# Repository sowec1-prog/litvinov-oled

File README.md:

# Litvínov OLED scoreboard

Autonomní hokejový panel pro **ESP32-C3 SuperMini** a OLED SSD1306 128×64. Firmware čte kompaktní stav z `https://litvinov-server.onrender.com/api/live`; PC ani LVGL nejsou potřeba.

## Funkce

- živé skóre, týmové kódy a poslední střelec bez diakritiky;
- `TRES-LIT`, `TRES-PCE` nebo `TRES-LIT/PCE` podle strukturované události píšťalky;
- přestávka s lokálním odpočtem bez cloudových dotazů;
- lokální odpočet příštího zápasu;
- gól Litvínova: znělka a 30sekundová blikající animace `GOOL` zprava doleva;
- první přijatý gól po restartu animaci ani zvuk nespustí;
- konečný výsledek se na cloudovém API drží pět minut jako `ZAPAS SKONCIL`.

## Použitý hardware

- **ESP32-C3 SuperMini** — ESP32-C3, 4 MB flash, Wi-Fi 2,4 GHz; projekt používá PlatformIO profil `esp32-c3-devkitm-1`.
- **OLED SSD1306 128 × 64 px**, I²C, adresa `0x3C`.
- **Pasivní piezo bzučák** ověřený pro PWM tóny.
- USB datový kabel pro napájení a nahrání firmwaru.
- Propojovací vodiče: 4× pro OLED, 2× pro bzučák.

## Zapojení

Všechny moduly musí mít společnou zem (**GND**). OLED i GPIO ESP32-C3 jsou 3,3 V logika; OLED proto napájejte z pinu **3V3**, ne z 5 V.

| ESP32-C3 SuperMini | Připojit na | Poznámka |
|---|---|---|
| GPIO8 | OLED SDA | I²C data |
| GPIO9 | OLED SCL | I²C hodiny |
| 3V3 | OLED VCC | napájení OLED |
| GND | OLED GND | společná zem |
| GPIO3 | piezo `+` / signál | PWM znělka — opravené zapojení PCB rev. A |
| GND | piezo `-` | společná zem |
| GPIO2 | ADC_BAT z děliče 100 kΩ / 100 kΩ | pouze připravený vstup měření baterie; firmware jej zatím nečte |

OLED používá I²C adresu `0x3C`.

### Oprava osazené PCB rev. A

Deska byla vyrobena s posunem dvou signálů proti původnímu návrhu: PWM bzučáku je na **GPIO3** (ne GPIO4) a uzel `ADC_BAT` děliče 100 kΩ / 100 kΩ vede na **GPIO2** (ne GPIO3). Firmware v této revizi používá GPIO3 pro bzučák; měření baterie zatím není implementované a GPIO2 proto nepoužívá. GPIO2 je bootovací pin ESP32-C3, takže před budoucím zapnutím měření baterie musí proběhnout fyzický boot test s osazeným děličem. `B+` článku se nikdy nesmí připojit přímo na GPIO.

## Doporučené vylepšení Wi-Fi antény

U ESP32-C3 SuperMini může mít jednoduchá úprava antény významný přínos pro slabší 2,4GHz signál. Pro Litvínov OLED byla prakticky ověřena rychlejší asociace k Wi-Fi a lepší RSSI po této úpravě. Postup a zkušenosti komunity: [ESP32-C3 SuperMini antenna mod](https://www.reddit.com/r/esp32/comments/1k01wtp/the_esp32c3_supermini_antenna_mod_is_the_real_deal/).

Jde o fyzickou pájecí úpravu modulu: dělejte ji jen při odpojeném USB napájení a na vlastní odpovědnost.

## Nastavení Wi-Fi

1. Zkopírujte `include/secrets.h.example` jako `include/secrets.h`.
2. Doplňte primární SSID/heslo a případně `WIFI_SSID_2` / `WIFI_PASSWORD_2` a `WIFI_SSID_3` / `WIFI_PASSWORD_3` pro další místa.
3. ESP32-C3 vybere první dostupnou uloženou 2,4GHz síť; po návratu domů se automaticky připojí k domácí Wi-Fi.
4. Pokud se žádná uložená síť nepřipojí do 45 sekund, OLED vytvoří zabezpečený hotspot **`Litvinov-OLED-Setup`** s heslem **`litvinov`**. Připojte se k němu telefonem, otevřete `http://192.168.4.1`, vyberte nalezenou síť a zadejte její heslo. Seznam obsahuje pouze 2,4GHz sítě kompatibilní s ESP32-C3.
5. Po úspěšném připojení hotspot zmizí; nově vybraná síť se uloží do paměti ESP spolu s dříve zadanými sítěmi.
6. Soubor `include/secrets.h` nikdy necommitujte; `.gitignore` jej vylučuje.

## Sestavení a nahrání

Vyžaduje PlatformIO a desku `esp32-c3-devkitm-1`.

```bash
uv run --with platformio pio run
uv run --with esptool esptool --chip esp32c3 --port COM3 --baud 460800 --no-stub write-flash \
  0x0 .pio/build/esp32-c3-devkitm-1/bootloader.bin \
  0x8000 .pio/build/esp32-c3-devkitm-1/partitions.bin \
  0x10000 .pio/build/esp32-c3-devkitm-1/firmware.bin
uv run --with esptool esptool --chip esp32c3 --port COM3 --baud 460800 --no-stub verify-flash \
  0x10000 .pio/build/esp32-c3-devkitm-1/firmware.bin
```

Předchozí funkční flash i zdrojová záloha zůstávají lokálně. Fyzické chování OLED a animace se ověřuje při skutečné nové události v přenosu.

## Použité knihovny

- Adafruit GFX 1.11.11
- Adafruit SSD1306 2.5.13
- ArduinoJson 7.1.0
- espressif32 6.7.0

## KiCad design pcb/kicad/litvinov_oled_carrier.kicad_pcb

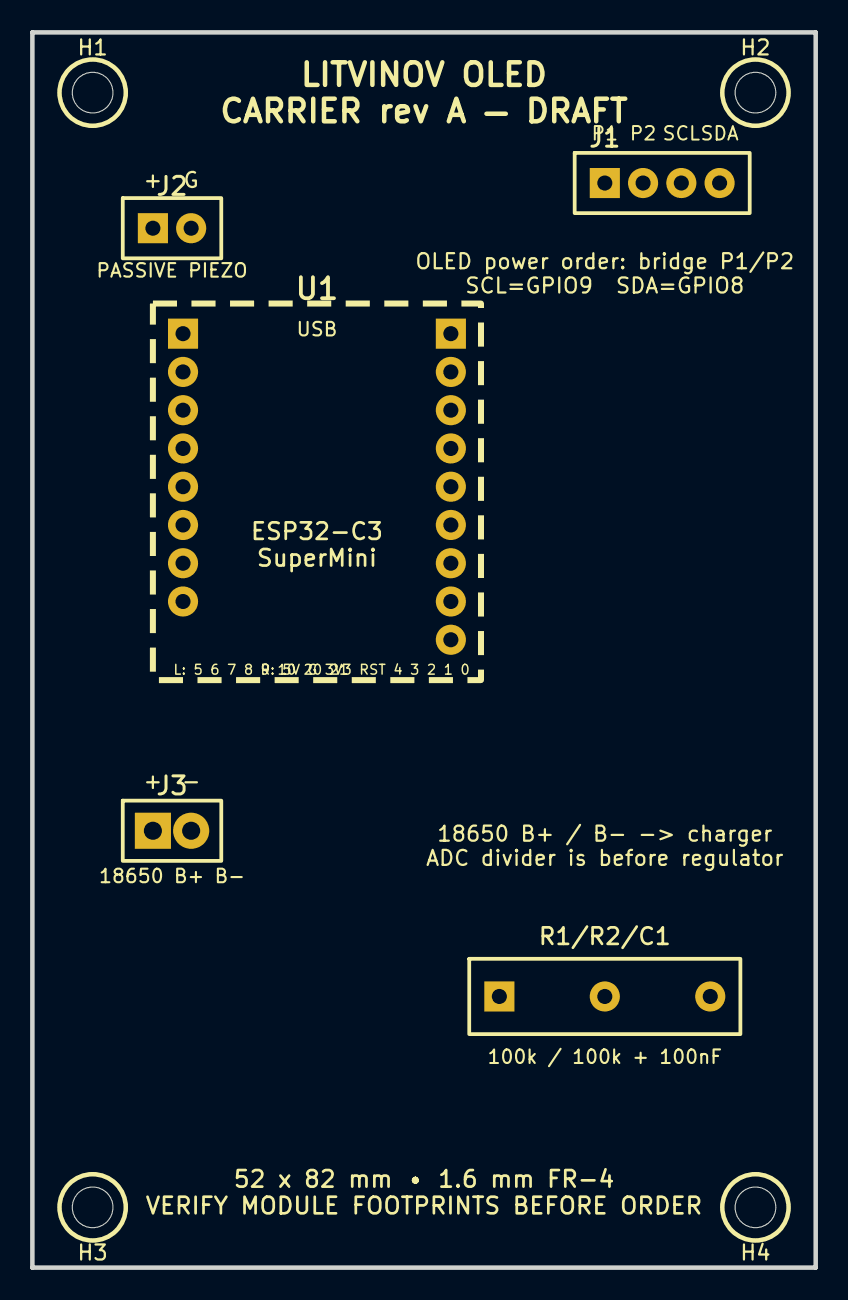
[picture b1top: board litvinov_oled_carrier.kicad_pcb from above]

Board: 2 copper layers, 52.0 x 82.0 mm, 9 parts (0 on the bottom side), 6 nets, no tracks yet.

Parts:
H1, H2, H3, H4: M2.5; MountingHole_2.5mm
J1: OLED 1x04: P1 P2 SCL SDA; OLED_1x04_2.54
J2: PASSIVE PIEZO; Buzzer_1x02_2.54
J3: 18650 B+ B-; Battery_1x02_2.54
R1/R2/C1: 100k / 100k + 100nF; ADC_Divider_100k_100k
U1: ESP32-C3 SuperMini; USB end is at top; ESP32-C3-SuperMini_1x08_1x09

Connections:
ADC_BAT_GPIO3: R1/R2/C1.ADC, U1.GPIO3
BATT_RAW: J3.1, R1/R2/C1.BATT
BUZZER_PWM_GPIO4: J2.1, U1.GPIO4
GND: J2.2, J3.2, R1/R2/C1.GND, U1.GND
I2C_SCL_GPIO9: J1.3, U1.GPIO9
I2C_SDA_GPIO8: J1.4, U1.GPIO8
